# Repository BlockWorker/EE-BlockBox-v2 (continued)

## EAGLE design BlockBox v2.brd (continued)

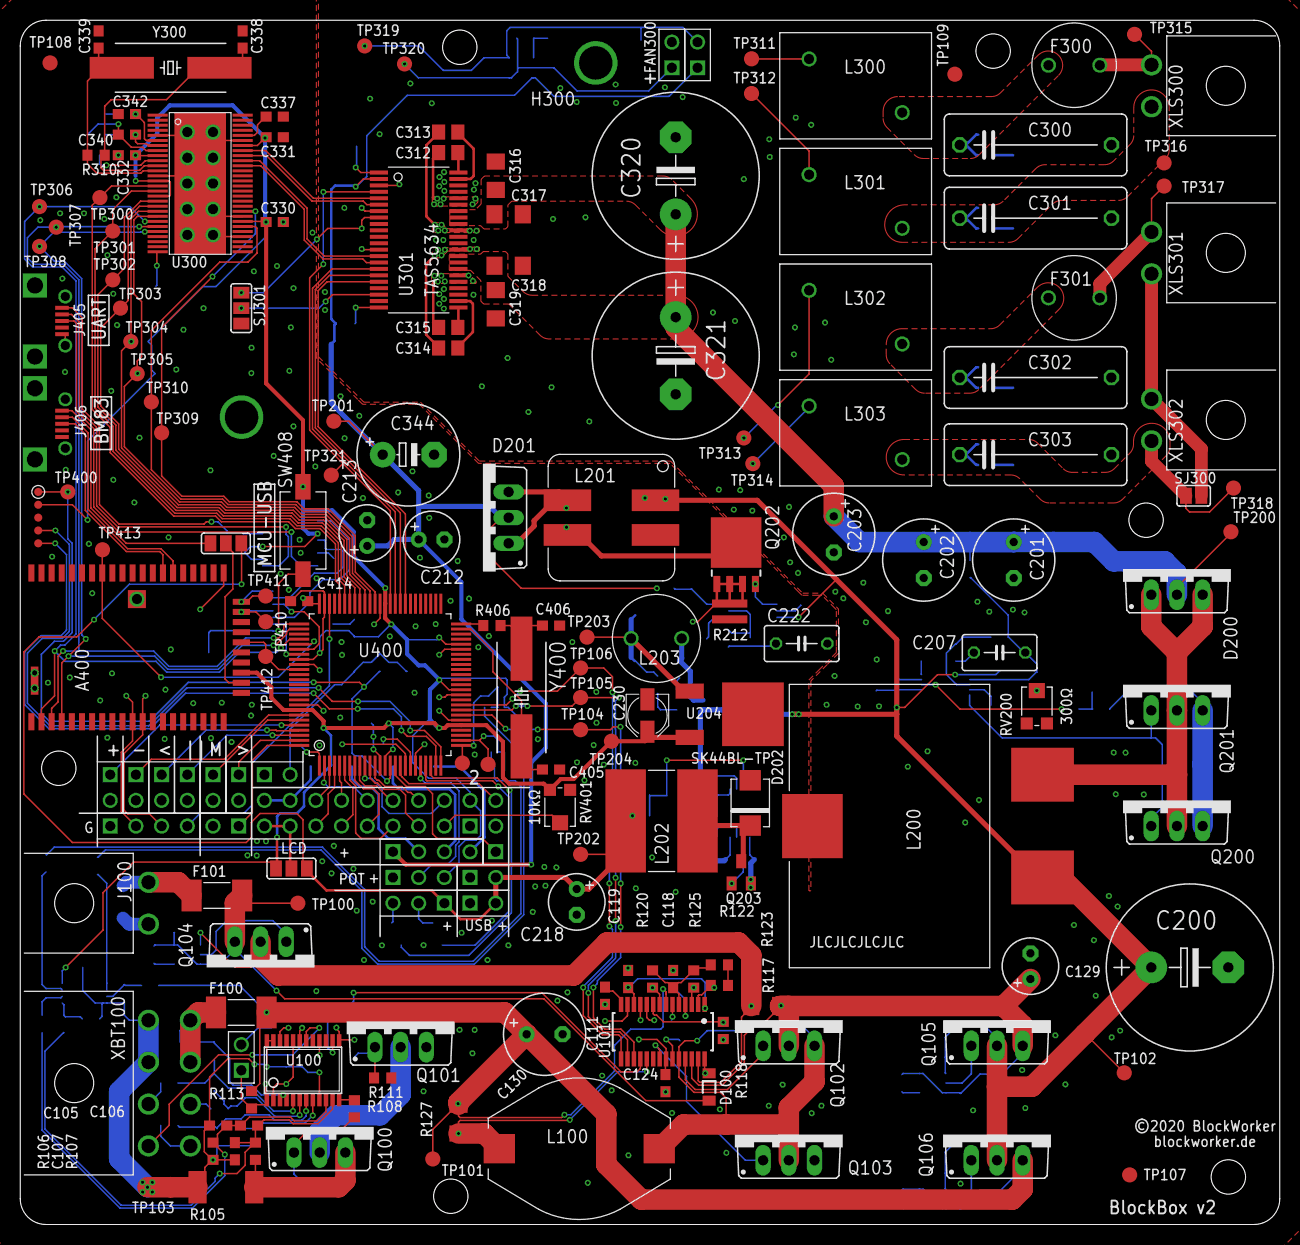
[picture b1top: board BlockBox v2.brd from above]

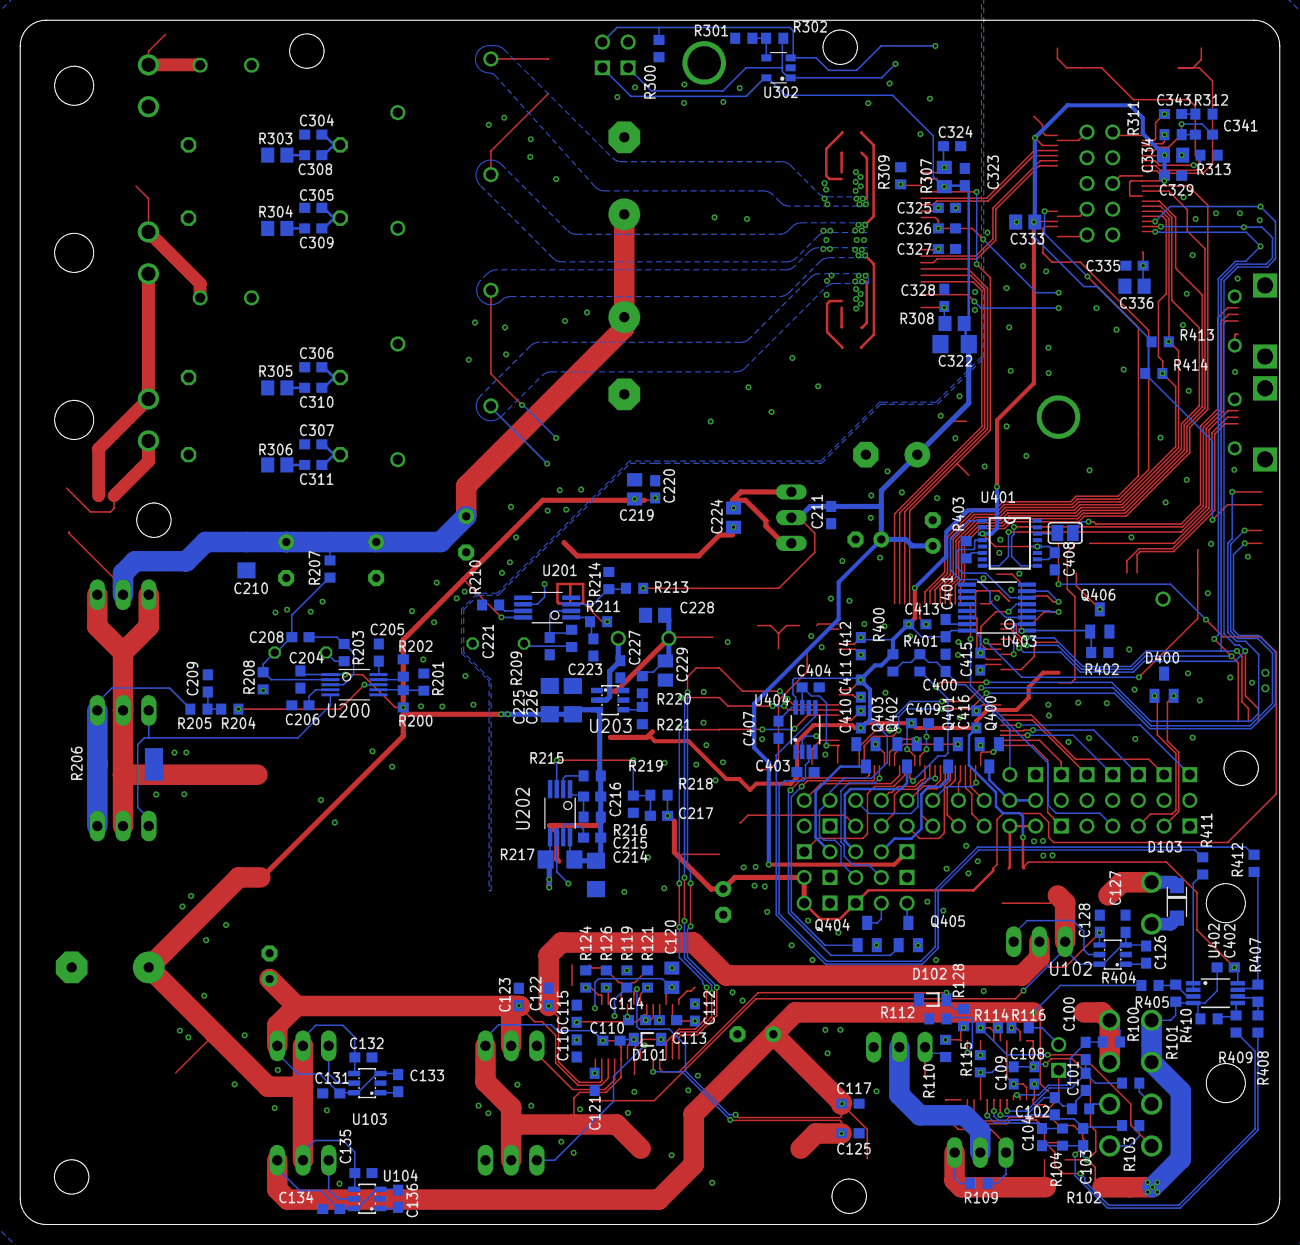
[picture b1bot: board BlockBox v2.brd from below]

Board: 2 copper layers, 124.5 x 119.0 mm, 350 parts (173 on the bottom side), 231 nets.

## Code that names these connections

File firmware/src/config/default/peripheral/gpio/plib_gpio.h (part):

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// *****************************************************************************
// *****************************************************************************

/*** Macros for LCD_BL_CTL pin ***/
#define LCD_BL_CTL_Set()               (LATGSET = (1<<15))
#define LCD_BL_CTL_Clear()             (LATGCLR = (1<<15))
#define LCD_BL_CTL_Toggle()            (LATGINV= (1<<15))
#define LCD_BL_CTL_Get()               ((PORTG >> 15) & 0x1)
#define LCD_BL_CTL_OutputEnable()      (TRISGCLR = (1<<15))
#define LCD_BL_CTL_InputEnable()       (TRISGSET = (1<<15))
#define LCD_BL_CTL_PIN                  GPIO_PIN_RG15
/*** Macros for LCD_ADDPIN pin ***/
#define LCD_ADDPIN_Set()               (LATASET = (1<<5))
#define LCD_ADDPIN_Clear()             (LATACLR = (1<<5))
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#define LCD_ADDPIN_OutputEnable()      (TRISACLR = (1<<5))
#define LCD_ADDPIN_InputEnable()       (TRISASET = (1<<5))
#define LCD_ADDPIN_PIN                  GPIO_PIN_RA5
/*** Macros for LCD_GPIO3 pin ***/
#define LCD_GPIO3_Set()               (LATESET = (1<<5))
#define LCD_GPIO3_Clear()             (LATECLR = (1<<5))
#define LCD_GPIO3_Toggle()            (LATEINV= (1<<5))
#define LCD_GPIO3_Get()               ((PORTE >> 5) & 0x1)
#define LCD_GPIO3_OutputEnable()      (TRISECLR = (1<<5))
#define LCD_GPIO3_InputEnable()       (TRISESET = (1<<5))
#define LCD_GPIO3_PIN                  GPIO_PIN_RE5
/*** Macros for LCD_GPIO2 pin ***/
#define LCD_GPIO2_Set()               (LATESET = (1<<6))
#define LCD_GPIO2_Clear()             (LATECLR = (1<<6))
#define LCD_GPIO2_Toggle()            (LATEINV= (1<<6))
#define LCD_GPIO2_Get()               ((PORTE >> 6) & 0x1)
#define LCD_GPIO2_OutputEnable()      (TRISECLR = (1<<6))
#define LCD_GPIO2_InputEnable()       (TRISESET = (1<<6))
#define LCD_GPIO2_PIN                  GPIO_PIN_RE6
/*** Macros for LCD_GPIO1 pin ***/
#define LCD_GPIO1_Set()               (LATESET = (1<<7))
#define LCD_GPIO1_Clear()             (LATECLR = (1<<7))
#define LCD_GPIO1_Toggle()            (LATEINV= (1<<7))
#define LCD_GPIO1_Get()               ((PORTE >> 7) & 0x1)
#define LCD_GPIO1_OutputEnable()      (TRISECLR = (1<<7))
#define LCD_GPIO1_InputEnable()       (TRISESET = (1<<7))
#define LCD_GPIO1_PIN                  GPIO_PIN_RE7
/*** Macros for LCD_GPIO0 pin ***/
#define LCD_GPIO0_Set()               (LATCSET = (1<<1))
#define LCD_GPIO0_Clear()             (LATCCLR = (1<<1))
#define LCD_GPIO0_Toggle()            (LATCINV= (1<<1))
#define LCD_GPIO0_Get()               ((PORTC >> 1) & 0x1)
#define LCD_GPIO0_OutputEnable()      (TRISCCLR = (1<<1))
#define LCD_GPIO0_InputEnable()       (TRISCSET = (1<<1))
#define LCD_GPIO0_PIN                  GPIO_PIN_RC1
/*** Macros for LCD_CS_N pin ***/
#define LCD_CS_N_Set()               (LATCSET = (1<<2))
#define LCD_CS_N_Clear()             (LATCCLR = (1<<2))
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#define BM_RST_N_OutputEnable()      (TRISDCLR = (1<<13))
#define BM_RST_N_InputEnable()       (TRISDSET = (1<<13))
#define BM_RST_N_PIN                  GPIO_PIN_RD13
/*** Macros for BM_MFB pin ***/
#define BM_MFB_Set()               (LATFSET = (1<<0))
#define BM_MFB_Clear()             (LATFCLR = (1<<0))
#define BM_MFB_Toggle()            (LATFINV= (1<<0))
#define BM_MFB_Get()               ((PORTF >> 0) & 0x1)
#define BM_MFB_OutputEnable()      (TRISFCLR = (1<<0))
#define BM_MFB_InputEnable()       (TRISFSET = (1<<0))
#define BM_MFB_PIN                  GPIO_PIN_RF0
/*** Macros for CTL_VOL_DOWN pin ***/
#define CTL_VOL_DOWN_Set()               (LATESET = (1<<1))
#define CTL_VOL_DOWN_Clear()             (LATECLR = (1<<1))
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
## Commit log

2020-01-08 Initial Commit.
2020-01-14 Audio path done, MCU project added
2020-01-18 MCU config done (for now), schematic base done
2020-01-18 Testpads added, schematic done (barring oversights)
2020-01-19 Some oversights fixed, minor additions.
2020-01-21 Test pads named, board started
2020-01-26 Major PCB progress, about to shrink PCB (safety commit)
2020-01-28 Voltage converter layout done
2020-02-05 PCB initially completed, final fixes
2020-02-05 Added logo and ground TPs
2020-02-06 Final PCB order adjustments
2020-02-26 Added laser cut and Fusion 360 data.
2020-02-28 Firmware beginnings.
2020-03-02 Firmware progress, speaker EQ start: woofer response
2020-03-03 Speaker EQ progress: finished base responses and HiFi EQ of new speakers
2020-03-06 Added speaker EQs for old speaker setup (v1) and power EQ for new setup
2020-03-15 Minor BM83 config changes, firmware progress (I2S + BM83 comms)
2020-03-17 Finished BM83 UART protocol (?), updated gitignore
2020-03-26 Fixed ridiculous labeling mistake.
2020-03-28 UART protocol finished, added debug UART port
2020-04-18 Major firmware progress, added CAM data
2020-06-01 Screen progress, CAD done(?)
2020-06-10 Major UI progress, started backing away from dynamic allocation
2020-06-11 Implemented battery energy estimation, made FT8 driver semi-static
2020-06-11 Fixed idiotic and expensive laser cut template mistake.
2020-07-15 Basic functionality established, lights implemented
2020-08-05 BM83 firmware update, display settings added (with display fadeout), other minor changes
2021-08-09 Display somehow not working again, safety commit before rework
2021-08-22 Implemented missing features, reworked EQs based on measurement
